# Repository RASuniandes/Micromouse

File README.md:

<h1 align="center">RAS Uniandes  - Micromouse 🐭🧀</h1>

### The autonomous maze-solving robot:

- SoB built around the STM32F405RGT6 
  - Wall detection based on peripheral infrared sensors and ToF
  - Position and speed control using magnetic encoders for Micro Metal Motors
  - IMU aided control
  - Bluetooth support
 
- Designed using KiCad
 
- Developed in the *Universidad de Los Andes* for the *Robotics and Automation Society* Chapter of the IEEE.

## Developed by: 
<ul>
  <li>Juan Sebastián Ortega Romero(https://github.com/tadzio8425)</li>
</ul>

## To do: 
- [x] Initial research regarding the state of the art of the competition
- [x] Selection of essential components 
- [x] Initial schematic design
- [x] Altium simulations
- [x] Infrared sensors breadboard testing
- [x] Schematic revisions and corrections
- [x] PCB Design and rule check
- [x] BOM File and quote requests
- [x] Final PCB revisions
- [x] Fabrication using the services of JLCPCB
- [x] Soldering components
- [x] Unitary tests
- [x] Coding Serial, USB and Bluetooth communications
- [x] Coding sensors
- [x] Coding a general version of the FloodFill algorithm in C
- [ ] Control and PID algorithm for position and speed
- [ ] Juncture of the control algorithm and FloodFill for maze solving
- [ ] Robot calibration in a real maze
- [ ] Development of external interfaces to ease communication with the robot

## Shematic

## PCB Design and 3D Render

| PCB | 3D |
| --- | --- |
|  |  | 

## Robot
| Initial Assembly | Final Version |
| --- | --- |
|  |  |

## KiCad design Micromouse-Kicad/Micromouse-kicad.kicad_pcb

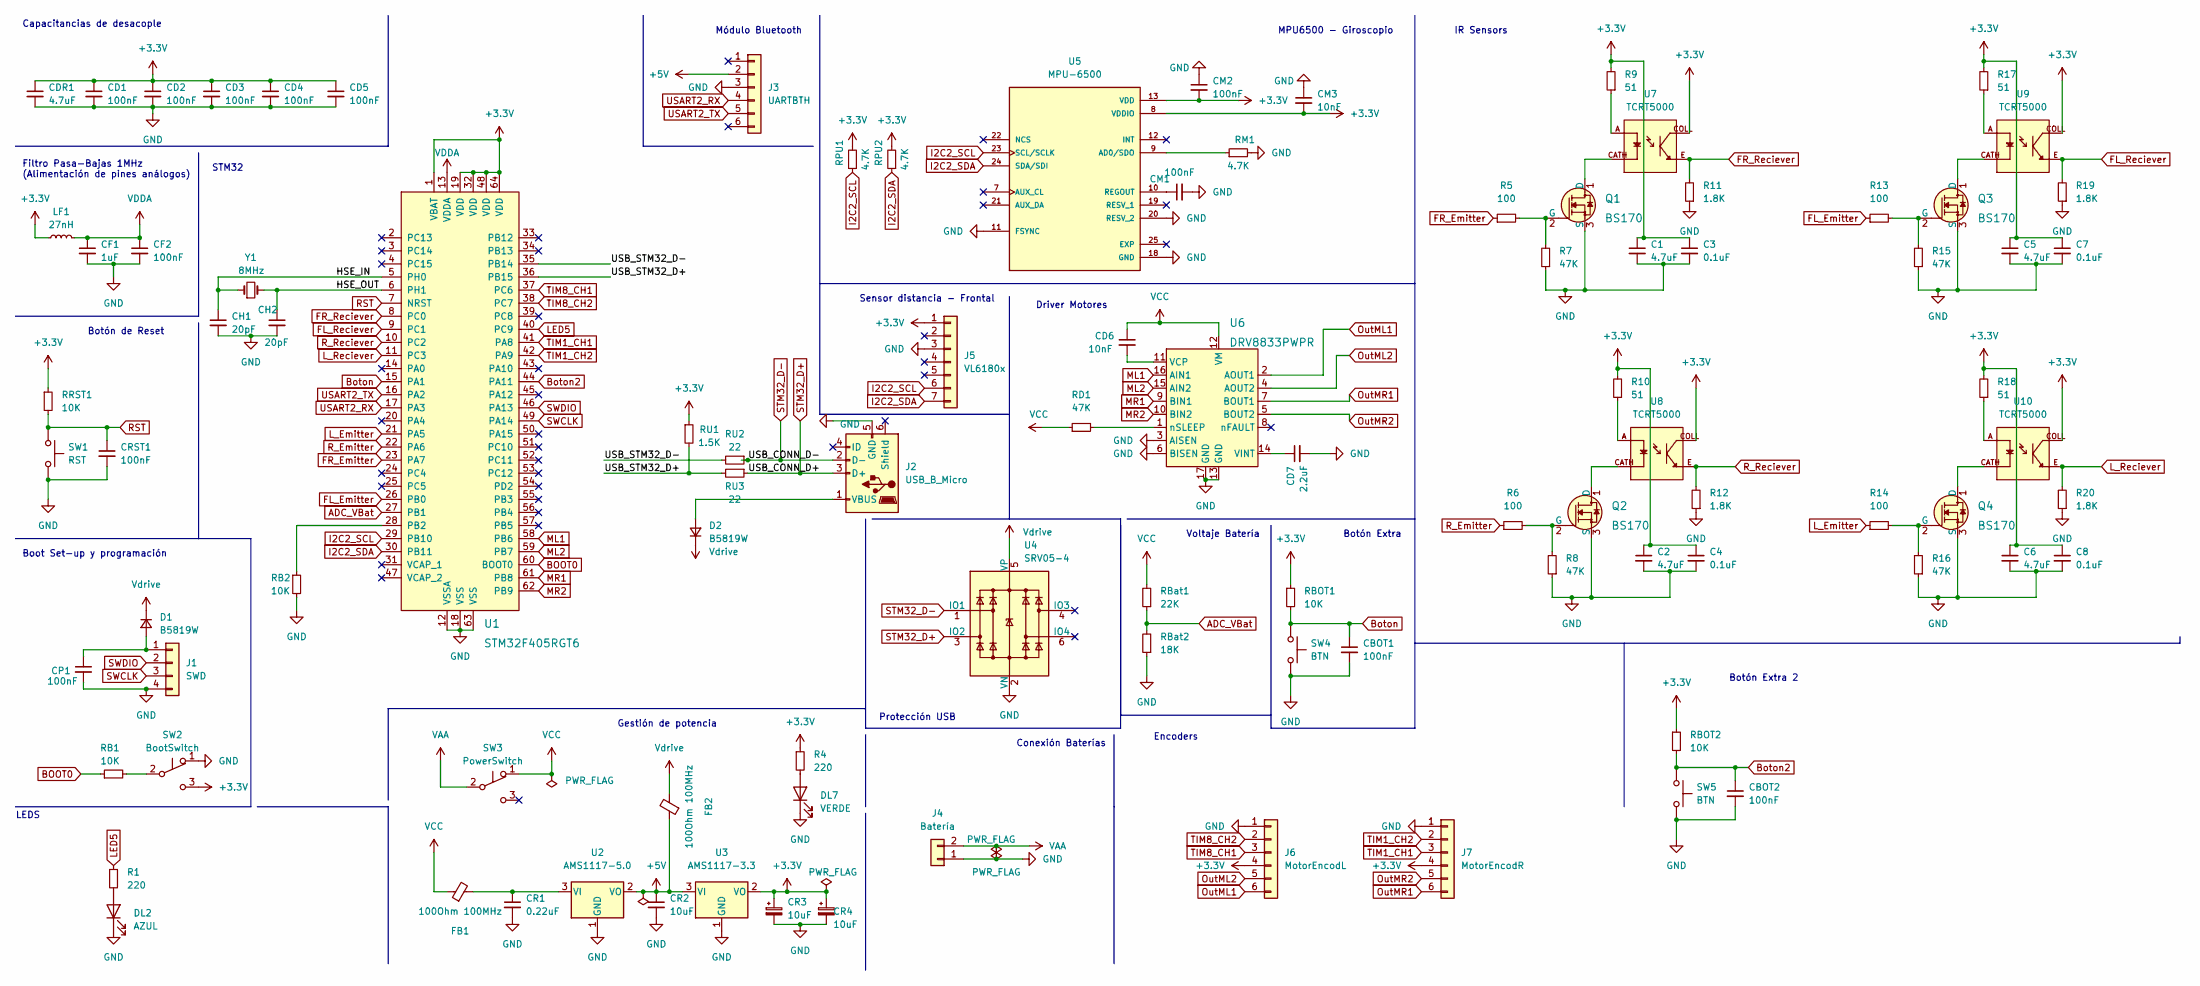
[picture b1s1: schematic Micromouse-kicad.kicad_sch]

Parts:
C1, C2, C5, C6: 4.7uF; C_0402_1005Metric
C3, C4, C7, C8: 0.1uF; C_0402_1005Metric
CBOT1, CBOT2: 100nF; C_0402_1005Metric
CD1, CD2, CD3, CD4, CD5: 100nF; C_0402_1005Metric
CD6: 10nF; C_0402_1005Metric
CD7: 2.2uF; C_0402_1005Metric
CDR1: 4.7uF; C_0402_1005Metric
CF1: 1uF; C_0402_1005Metric
CF2: 100nF; C_0402_1005Metric
CH1, CH2: 20pF; C_0402_1005Metric
CM1, CM2: 100nF; C_0402_1005Metric
CM3: 10nF; C_0402_1005Metric
CP1: 100nF; C_0402_1005Metric
CR1: 0.22uF; C_1206_3216Metric
CR2, CR3, CR4: 10uF; C_1206_3216Metric
CRST1: 100nF; C_0402_1005Metric
D1, D2: B5819W; D_SOD-123
DL2: AZUL; LED_0603_1608Metric
DL7: VERDE; LED_0603_1608Metric
FB1, FB2: 100Ohm 100MHz; L_0805_2012Metric
J1: SWD; PinHeader_1x04_P2.54mm_Vertical
J2: USB_B_Micro; MICRO-USB-SMD_5P-P0.65-H-F_MICRO5.9MMUSB
J3: UARTBTH; PinSocket_1x06_P2.54mm_Vertical
J4: Batería; AMASS_XT60-M
J5: VL6180x; PinSocket_1x07_P2.54mm_Vertical
J6: MotorEncodL; JST_SH_BM06B-SRSS-TB_1x06-1MP_P1.00mm_Vertical
J7: MotorEncodR; JST_SH_BM06B-SRSS-TB_1x06-1MP_P1.00mm_Vertical
LF1: 27nH; L_0402_1005Metric
Q1, Q2, Q3, Q4: BS170; TO-92-3; MPN BS170; Digi-Key_PN BS170-ND
R1, R4: 220; R_0603_1608Metric
R5, R6, R13, R14: 100; R_0402_1005Metric
R7, R8, R15, R16: 47K; R_0402_1005Metric
R9, R10, R17, R18: 51; R_0402_1005Metric
R11, R12, R19, R20: 1.8K; R_0402_1005Metric
RB1, RB2: 10K; R_0402_1005Metric
RBOT1, RBOT2: 10K; R_0402_1005Metric
RBat1: 22K; R_0402_1005Metric
RBat2: 18K; R_0402_1005Metric
RD1: 47K; R_0402_1005Metric
RM1: 4.7K; R_0402_1005Metric
RPU1, RPU2: 4.7K; R_0402_1005Metric
RRST1: 10K; R_0402_1005Metric
RU1: 1.5K; R_0402_1005Metric
RU2, RU3: 22; R_0603_1608Metric
SW1: RST; SW_PUSH_6mm_H5mm
SW2: BootSwitch; Switch_Slide
SW3: PowerSwitch; Switch_Slide
SW4, SW5: BTN; SW_PUSH_6mm_H5mm
U1: STM32F405RGT6; LQFP-64_10x10mm; MPN STM32F405RGT6; Digi-Key_PN 497-11767-ND
U2: AMS1117-5.0; SOT-223-3_TabPin2
U3: AMS1117-3.3; SOT-223-3_TabPin2
U4: SRV05-4; SOT-23-6
U5: MPU-6500; QFN40P300X300X95-25N; PARTREV 1.3
U6: DRV8833PWPR; TSSOP-16-1EP_W4.40mm; MPN DRV8833PWPR; Digi-Key_PN 296-29434-1-ND
U7, U8, U9, U10: TCRT5000; OPTO_TCRT5000; PARTREV 1.7
Y1: 8MHz; Crystal_SMD_5032-2Pin_5.0x3.2mm

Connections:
+3.3V: C1.1, C2.1, C3.1, C4.1, C5.1, C6.1, C7.1, C8.1, CD1.1, CD2.1, CD3.1, CD4.1, CD5.1, CDR1.1, CM2.2, CM3.2, CR3.1, CR4.1, J5.1, J6.4, J7.4, LF1.1, R4.1, R9.2, R10.2, R17.2, R18.2, RBOT1.1, RBOT2.1, RPU1.2, RPU2.2, RRST1.1, RU1.1, SW2.3 (C), U1.1 (VBAT), U1.19 (VDD), U1.32 (VDD), U1.48 (VDD), U1.64 (VDD), U3.2 (VO), U5.8 (VDDIO), U5.13 (VDD), U7.COLL, U8.COLL, U9.COLL, U10.COLL
+5V: CR2.1, FB2.1, J3.2, U2.2 (VO), U3.3 (VI)
/HSE_IN: CH1.1, U1.5 (PH0), Y1.1
/HSE_OUT: CH2.1, U1.6 (PH1), Y1.2
/USB_STM32_D+: RU1.2, RU3.2, U1.36 (PB15)
/USB_STM32_D-: RU2.2, U1.35 (PB14)
ADC_VBat: RBat1.1, RBat2.2, U1.27 (PB1)
BOOT0: RB1.1, U1.60 (BOOT0)
Boton: CBOT1.1, RBOT1.2, SW4.1, U1.15 (PA1)
Boton2: CBOT2.1, RBOT2.2, SW5.1, U1.44 (PA11)
FL_Emitter: R13.1, U1.26 (PB0)
FL_Reciever: R19.2, U1.9 (PC1), U9.E
FR_Emitter: R5.1, U1.23 (PA7)
FR_Reciever: R11.2, U1.8 (PC0), U7.E
GND: C1.2, C2.2, C3.2, C4.2, C5.2, C6.2, C7.2, C8.2, CBOT1.2, CBOT2.2, CD1.2, CD2.2, CD3.2, CD4.2, CD5.2, CD7.2, CDR1.2, CF1.2, CF2.2, CH1.2, CH2.2, CM1.2, CM2.1, CM3.1, CP1.2, CR1.2, CR2.2, CR3.2, CR4.2, CRST1.2, DL2.1 (K), DL7.1 (K), J1.4, J2.5 (GND), J3.3, J4.1, J5.3, J6.1, J7.1, Q1.3 (S), Q2.3 (S), Q3.3 (S), Q4.3 (S), R7.1, R8.1, R11.1, R12.1, R15.1, R16.1, R19.1, R20.1, RB2.2, RBat2.1, RM1.2, SW1.2, SW2.1 (A), SW4.2, SW5.2, U1.12 (VSSA), U1.18 (VSS), U1.63 (VSS), U2.1 (GND), U3.1 (GND), U4.2 (VN), U5.11 (FSYNC), U5.18 (GND), U5.20 (RESV_2), U6.3 (AISEN), U6.6 (BISEN), U6.13 (GND), U6.17 (GND)
I2C2_SCL: J5.6, RPU1.1, U1.29 (PB10), U5.23 (SCL/SCLK)
I2C2_SDA: J5.7, RPU2.1, U1.30 (PB11), U5.24 (SDA/SDI)
LED5: R1.1, U1.40 (PC9)
L_Emitter: R14.1, U1.21 (PA5)
L_Reciever: R20.2, U1.11 (PC3), U10.E
ML1: U1.58 (PB6), U6.16 (AIN1)
ML2: U1.59 (PB7), U6.15 (AIN2)
MR1: U1.61 (PB8), U6.9 (BIN1)
MR2: U1.62 (PB9), U6.10 (BIN2)
unnamed: CP1.1, D1.2 (A), J1.1
unnamed: D2.2 (A), J2.1 (VBUS)
unnamed: DL2.2 (A), R1.2
unnamed: DL7.2 (A), R4.2
unnamed: Q1.1 (D), U7.CATH
unnamed: Q1.2 (G), R5.2, R7.2
unnamed: Q2.1 (D), U8.CATH
unnamed: Q2.2 (G), R6.2, R8.2
unnamed: Q3.1 (D), U9.CATH
unnamed: Q3.2 (G), R13.2, R15.2
unnamed: Q4.1 (D), U10.CATH
unnamed: Q4.2 (G), R14.2, R16.2
unnamed: R9.1, U7.A
unnamed: R10.1, U8.A
unnamed: R17.1, U9.A
unnamed: R18.1, U10.A
unnamed: RB1.2, SW2.2 (B)
unnamed: RB2.1, U1.28 (PB2)
unnamed: CR1.1, FB1.2, U2.3 (VI)
unnamed: RM1.1, U5.9 (AD0/SDO)
unnamed: CM1.1, U5.10 (REGOUT)
unnamed: CD6.2, U6.11 (VCP)
unnamed: CD7.1, U6.14 (VINT)
unnamed: RD1.2, U6.1 (nSLEEP)
OutML1: J6.6, U6.2 (AOUT1)
OutML2: J6.5, U6.4 (AOUT2)
OutMR1: J7.6, U6.7 (BOUT1)
OutMR2: J7.5, U6.5 (BOUT2)
RST: CRST1.1, RRST1.2, SW1.1, U1.7 (NRST)
R_Emitter: R6.1, U1.22 (PA6)
R_Reciever: R12.2, U1.10 (PC2), U8.E
STM32_D+: J2.3 (D+), RU3.1, U4.3 (IO2)
STM32_D-: J2.2 (D-), RU2.1, U4.1 (IO1)
SWCLK: J1.3, U1.49 (PA14)
SWDIO: J1.2, U1.46 (PA13)
TIM1_CH1: J7.3, U1.41 (PA8)
TIM1_CH2: J7.2, U1.42 (PA9)
TIM8_CH1: J6.3, U1.37 (PC6)
TIM8_CH2: J6.2, U1.38 (PC7)
USART2_RX: J3.4, U1.17 (PA3)
USART2_TX: J3.5, U1.16 (PA2)
VAA: J4.2, SW3.2 (B)
VCC: CD6.1, FB1.1, RBat1.2, RD1.1, SW3.1 (A), U6.12 (VM)
VDDA: CF1.1, CF2.1, LF1.2, U1.13 (VDDA)
Vdrive: D1.1 (K), D2.1 (K), FB2.2, U4.5 (VP)

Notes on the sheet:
Protección USB
Voltaje Batería
LEDS
Gestión de potencia
Conexión Baterías
MPU6500 - Giroscopio
Botón Extra
STM32
IR Sensors
Módulo Bluetooth
Botón de Reset
Encoders
Botón Extra 2
Driver Motores
Capacitancias de desacople
Boot Set-up y programación
Filtro Pasa-Bajas 1MHz (Alimentación de pines análogos)
Sensor distancia - Frontal

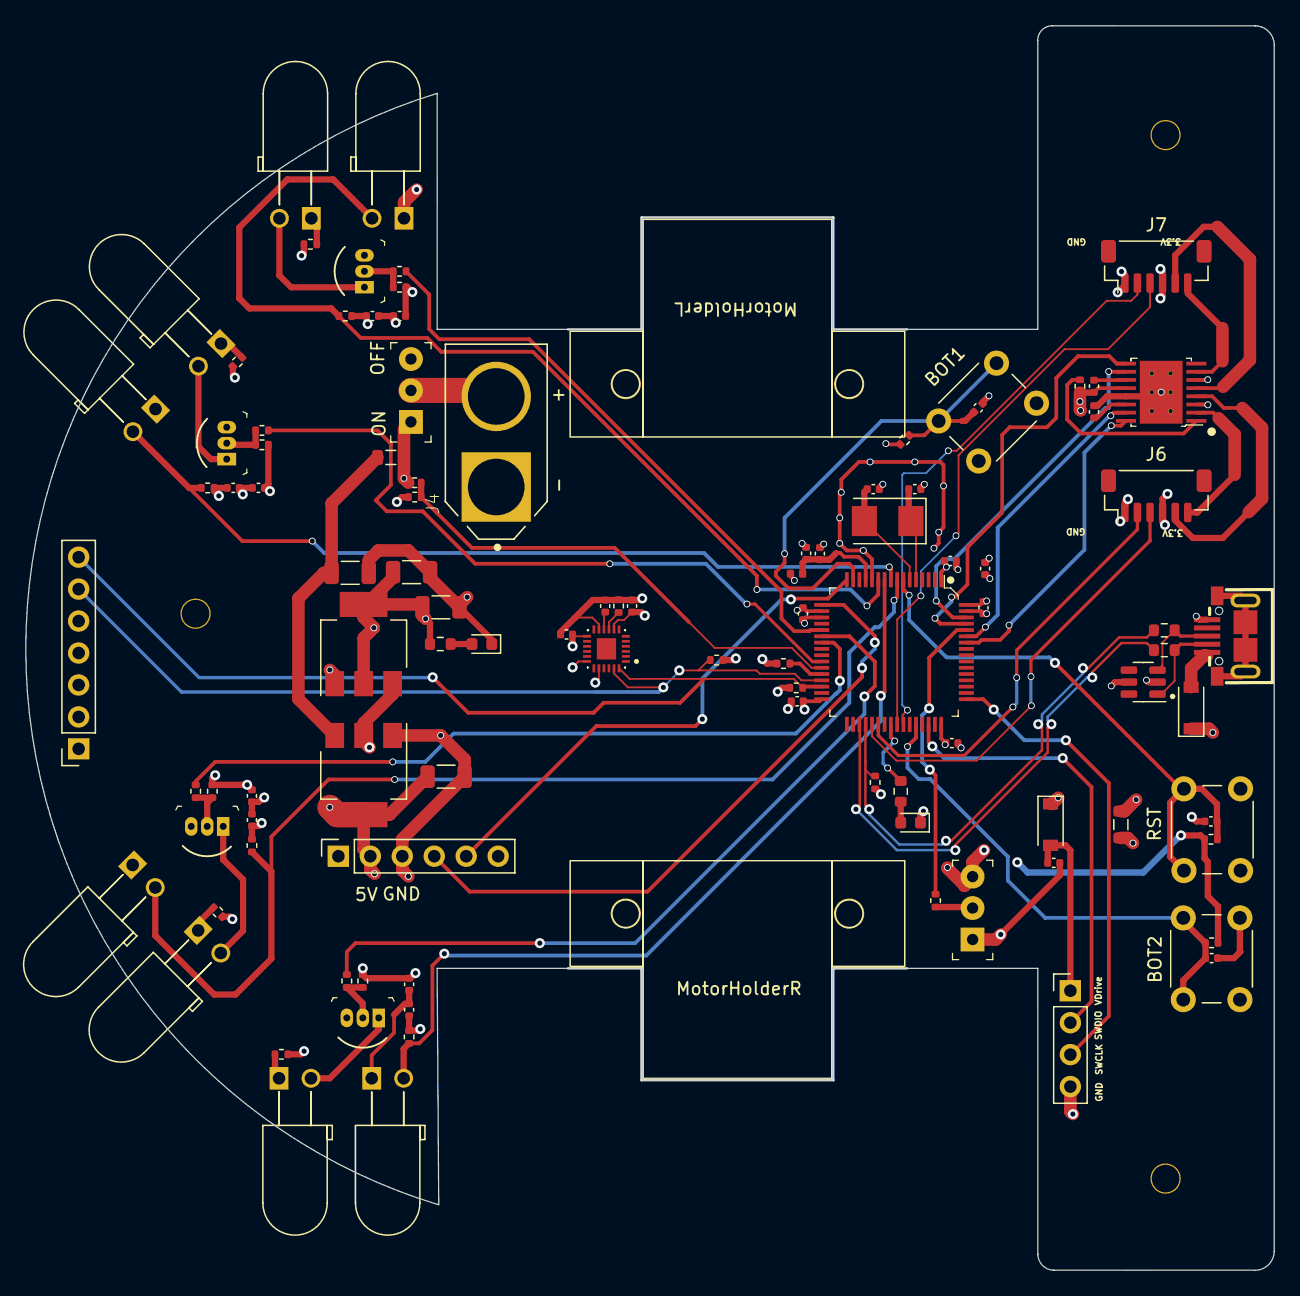
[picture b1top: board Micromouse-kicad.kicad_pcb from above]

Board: 4 copper layers, 99.1 x 98.8 mm, 99 parts (0 on the bottom side), 69 nets.

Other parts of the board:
MotorHolderL: Pololu; MotorHolder
MotorHolderR: Pololu; MotorHolder

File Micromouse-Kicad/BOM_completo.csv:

Id;Identificador;Empaquetado;Cantidad;Identificación;#Ref DigiKey ;Cantidad pedida;PPU ($);Total ($)
1;RBOT1,RB2,RBOT2,RRST1,RB1;R_0402_1005Metric;5;10K;RC1005F103CS;10;0.055;0.55
2;SW1;SW_PUSH_6mm_H5mm;1;RST;;;;0
3;R20,R11,R19,R12;R_0402_1005Metric;4;1.8K;RC0402FR-071K8L;10;0.014;0.14
4;CRST1,CP1,CF2,CM2,CD4,CBOT1,CBOT2,CD3,CM1,CD5,CD2,CD1;C_0402_1005Metric;12;100nF;;;;0
5;C6,CDR1,C1,C2,C5;C_0402_1005Metric;5;4.7uF;;;;0
6;U3;SOT-223-3_TabPin2;1;AMS1117-3.3;;;;0
7;Q1,Q4,Q3,Q2;TO-92-3;4;BS170;;;;0
8;RU1;R_0402_1005Metric;1;1.5K;RC0402FR-071K5L;10;0.014;0.14
9;RPU1,RM1,RPU2;R_0402_1005Metric;3;4.7K;AF0402FR-074K7L;10;0.053;0.53
10;R15,R16,R8,R7,RD1;R_0402_1005Metric;5;47K;AF0402FR-0747KL;10;0.053;0.53
11;DL7;LED_0603_1608Metric;1;VERDE;;;;0
12;U5;QFN40P300X300X95-25N;1;MPU-6500;1428-1011-1-ND;1;9.11;9.11
13;J2;MICRO-USB-SMD_5P-P0.65-H-F_MICRO5.9MMUSB;1;USB_B_Micro;;;;0
14;CD7;C_0402_1005Metric;1;2.2uF;;;;0
15;RU2,RU3;R_0603_1608Metric;2;22;;;;0
16;U6;TSSOP-16-1EP_W4.40mm;1;DRV8833PWPR;;;;0
17;LF1;L_0402_1005Metric;1;27nH;;;;0
18;CF1;C_0402_1005Metric;1;1uF;;;;0
19;R5,R13,R14,R6;R_0402_1005Metric;4;100;;;;0
20;R9,R18,R10,R17;R_0402_1005Metric;4;51;;;;0
21;U8,U9,U10,U7;OPTO_TCRT5000;4;TCRT5000;;;;0
22;C4,C8,C7,C3;C_0402_1005Metric;4;0.1uF;;;;0
23;J4;AMASS_XT60-M;1;BaterÃ­a;;;;0
24;CR4,CR3,CR2;C_1206_3216Metric;3;10uF;;;;0
25;SW2;Switch_Slide;1;BootSwitch;;;;0
26;FB1,FB2;L_0805_2012Metric;2;100Ohm 100MHz;;;;0
27;Y1;Crystal_SMD_5032-2Pin_5.0x3.2mm;1;8MHz;;;;0
28;MotorHolderR,MotorHolderL;MotorHolder;2;Pololu;;;;0
29;J3;PinSocket_1x06_P2.54mm_Vertical;1;UARTBTH;;;;0
30;DL2;LED_0603_1608Metric;1;AZUL;;;;0
31;J6;JST_SH_BM06B-SRSS-TB_1x06-1MP_P1.00mm_Vertical;1;MotorEncodL;;;;0
32;U2;SOT-223-3_TabPin2;1;AMS1117-5.0;;;;0
33;J5;PinSocket_1x07_P2.54mm_Vertical;1;VL6180x ;;;;0
34;SW5,SW4;SW_PUSH_6mm_H5mm;2;BTN;;;;0
35;U4;SOT-23-6;1;SRV05-4;;;;0
36;R1,R4;R_0603_1608Metric;2;220;;;;0
37;J7;JST_SH_BM06B-SRSS-TB_1x06-1MP_P1.00mm_Vertical;1;MotorEncodR;;;;0
38;CD6,CM3;C_0402_1005Metric;2;10nF;;;;0
39;D2,D1;D_SOD-123;2;B5819W;;;;0
40;RBat1;R_0402_1005Metric;1;22K;;;;0
41;RBat2;R_0402_1005Metric;1;18K;;;;0
42;SW3;Switch_Slide;1;PowerSwitch;;;;0
43;U1;LQFP-64_10x10mm;1;STM32F405RGT6;;;;0
44;CH1,CH2;C_0402_1005Metric;2;20pF;;;;0
45;CR1;C_1206_3216Metric;1;0.22uF;;;;0
46;J1;PinHeader_1x04_P2.54mm_Vertical;1;SWD;;;;0

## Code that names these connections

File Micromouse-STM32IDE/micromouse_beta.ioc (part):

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Mcu.Name=STM32F405RGTx
Mcu.Package=LQFP64
Mcu.UserName=STM32F405RGTx
PA1.GPIOParameters=GPIO_Label
PA1.GPIO_Label=BOTON1
PA1.Signal=GPIO_Input
PA11.GPIOParameters=GPIO_Label
PA11.GPIO_Label=BOTON2
PA11.Signal=GPIO_Input
PA13.Mode=Serial_Wire
PA13.Signal=SYS_JTMS-SWDIO
PA14.Mode=Serial_Wire
PA14.Signal=SYS_JTCK-SWCLK
PA2.Mode=Asynchronous
PA2.Signal=USART2_TX
PA3.Mode=Asynchronous
PA3.Signal=USART2_RX
PA5.GPIOParameters=GPIO_Label
PA5.GPIO_Label=R_Emitter
PA5.Signal=GPIO_Output
PA6.GPIOParameters=GPIO_Label
PA6.GPIO_Label=L_Emitter
PA6.Signal=GPIO_Output
PA7.GPIOParameters=GPIO_Label
PA7.GPIO_Label=FL_Emitter
PA7.Signal=GPIO_Output
PA8.Signal=S_TIM1_CH1
PA9.Signal=S_TIM1_CH2
PB0.GPIOParameters=GPIO_Label
PB0.GPIO_Label=FR_Emitter
PB0.Signal=GPIO_Output
PB1.GPIOParameters=GPIO_Label
PB1.GPIO_Label=vBat
PB1.Signal=ADCx_IN9
PB10.Mode=I2C
PB10.Signal=I2C2_SCL
PB11.Mode=I2C
PB11.Signal=I2C2_SDA
PB14.Mode=Device_Only_FS
PB14.Signal=USB_OTG_HS_DM
PB15.Mode=Device_Only_FS
PB15.Signal=USB_OTG_HS_DP
PB6.Signal=S_TIM4_CH1
PB7.Signal=S_TIM4_CH2
PB8.Signal=S_TIM4_CH3
PB9.Signal=S_TIM4_CH4
PC0.GPIOParameters=GPIO_Label
PC0.GPIO_Label=FL_Reciever
PC0.Signal=ADCx_IN10
PC1.GPIOParameters=GPIO_Label
PC1.GPIO_Label=FR_Reciever
PC1.Signal=ADCx_IN11
PC2.GPIOParameters=GPIO_Label
PC2.GPIO_Label=L_Reciever
PC2.Signal=ADCx_IN12
PC3.GPIOParameters=GPIO_Label
PC3.GPIO_Label=R_Reciever
PC3.Signal=ADCx_IN13
PC6.Signal=S_TIM8_CH1
PC7.Signal=S_TIM8_CH2
PC9.GPIOParameters=GPIO_Label
PC9.GPIO_Label=BLUE
PC9.Signal=GPIO_Output
PH0-OSC_IN.Mode=HSE-External-Oscillator
PH0-OSC_IN.Signal=RCC_OSC_IN
PH1-OSC_OUT.Mode=HSE-External-Oscillator
PH1-OSC_OUT.Signal=RCC_OSC_OUT
RCC.HSE_VALUE=8000000
RCC.SYSCLKFreq_VALUE=168000000
RCC.SYSCLKSource=RCC_SYSCLKSOURCE_PLLCLK
board=custom

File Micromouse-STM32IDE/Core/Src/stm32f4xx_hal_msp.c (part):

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
    __HAL_RCC_GPIOC_CLK_ENABLE();
    /**ADC1 GPIO Configuration
    PC0     ------> ADC1_IN10
    PC1     ------> ADC1_IN11
    PC2     ------> ADC1_IN12
    PC3     ------> ADC1_IN13
    */
    GPIO_InitStruct.Pin = FL_Reciever_Pin|FR_Reciever_Pin|L_Reciever_Pin|R_Reciever_Pin;
    GPIO_InitStruct.Mode = GPIO_MODE_ANALOG;
    GPIO_InitStruct.Pull = GPIO_NOPULL;
    HAL_GPIO_Init(GPIOC, &GPIO_InitStruct);
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
    __HAL_RCC_GPIOB_CLK_ENABLE();
    /**ADC2 GPIO Configuration
    PB1     ------> ADC2_IN9
    */
    GPIO_InitStruct.Pin = vBat_Pin;
    GPIO_InitStruct.Mode = GPIO_MODE_ANALOG;
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    __HAL_RCC_ADC1_CLK_DISABLE();

    /**ADC1 GPIO Configuration
    PC0     ------> ADC1_IN10
    PC1     ------> ADC1_IN11
    PC2     ------> ADC1_IN12
    PC3     ------> ADC1_IN13
    */
    HAL_GPIO_DeInit(GPIOC, FL_Reciever_Pin|FR_Reciever_Pin|L_Reciever_Pin|R_Reciever_Pin);

    /* ADC1 DMA DeInit */
    HAL_DMA_DeInit(hadc->DMA_Handle);
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    __HAL_RCC_ADC2_CLK_DISABLE();

    /**ADC2 GPIO Configuration
    PB1     ------> ADC2_IN9
    */
    HAL_GPIO_DeInit(vBat_GPIO_Port, vBat_Pin);

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
    __HAL_RCC_GPIOB_CLK_ENABLE();
    /**I2C2 GPIO Configuration
    PB10     ------> I2C2_SCL
    PB11     ------> I2C2_SDA
    */
    GPIO_InitStruct.Pin = GPIO_PIN_10|GPIO_PIN_11;
    GPIO_InitStruct.Mode = GPIO_MODE_AF_OD;
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    __HAL_RCC_I2C2_CLK_DISABLE();

    /**I2C2 GPIO Configuration
    PB10     ------> I2C2_SCL
    PB11     ------> I2C2_SDA
    */
    HAL_GPIO_DeInit(GPIOB, GPIO_PIN_10);

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
    __HAL_RCC_GPIOA_CLK_ENABLE();
    /**TIM1 GPIO Configuration
    PA8     ------> TIM1_CH1
    PA9     ------> TIM1_CH2
    */
    GPIO_InitStruct.Pin = GPIO_PIN_8|GPIO_PIN_9;
    GPIO_InitStruct.Mode = GPIO_MODE_AF_PP;
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
    __HAL_RCC_GPIOC_CLK_ENABLE();
    /**TIM8 GPIO Configuration
    PC6     ------> TIM8_CH1
    PC7     ------> TIM8_CH2
    */
    GPIO_InitStruct.Pin = GPIO_PIN_6|GPIO_PIN_7;
    GPIO_InitStruct.Mode = GPIO_MODE_AF_PP;
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
    __HAL_RCC_GPIOB_CLK_ENABLE();
    /**TIM4 GPIO Configuration
    PB6     ------> TIM4_CH1
    PB7     ------> TIM4_CH2
    PB8     ------> TIM4_CH3
    PB9     ------> TIM4_CH4
    */
    GPIO_InitStruct.Pin = GPIO_PIN_6|GPIO_PIN_7|GPIO_PIN_8|GPIO_PIN_9;
    GPIO_InitStruct.Mode = GPIO_MODE_AF_PP;
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    __HAL_RCC_TIM1_CLK_DISABLE();

    /**TIM1 GPIO Configuration
    PA8     ------> TIM1_CH1
    PA9     ------> TIM1_CH2
    */
    HAL_GPIO_DeInit(GPIOA, GPIO_PIN_8|GPIO_PIN_9);

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    __HAL_RCC_TIM8_CLK_DISABLE();

    /**TIM8 GPIO Configuration
    PC6     ------> TIM8_CH1
    PC7     ------> TIM8_CH2
    */
    HAL_GPIO_DeInit(GPIOC, GPIO_PIN_6|GPIO_PIN_7);

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
    __HAL_RCC_GPIOA_CLK_ENABLE();
    /**USART2 GPIO Configuration
    PA2     ------> USART2_TX
    PA3     ------> USART2_RX
    */
    GPIO_InitStruct.Pin = GPIO_PIN_2|GPIO_PIN_3;
    GPIO_InitStruct.Mode = GPIO_MODE_AF_PP;
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    __HAL_RCC_USART2_CLK_DISABLE();

    /**USART2 GPIO Configuration
    PA2     ------> USART2_TX
    PA3     ------> USART2_RX
    */
    HAL_GPIO_DeInit(GPIOA, GPIO_PIN_2|GPIO_PIN_3);

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
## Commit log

2022-12-23 readme creado
2022-12-23 readme creaso
2022-12-23 Commit inicial
2022-12-24 Avance esquemático - STM32, MPU6500, Driver Motores
2022-12-24 Esquemático con componentes básicos
2022-12-24 Huellas agregadas
2022-12-26 Avance PCB - Forma y motores
2022-12-27 Motores routeados
2022-12-27 MPU6500 routeado
2022-12-27 Casi todo routeado
2022-12-27 PCB Completa - Depurada
2022-12-27 Arreglo silkscreen
2022-12-27 Gerber generados
2022-12-27 BOM provisional
2022-12-27 Primera iteración finalizada
2022-12-27 Modelo 3D
2022-12-27 Sensor IR Modelado
2022-12-27 Cabra
2022-12-27 Ajuste VL180X
2023-01-06 Arreglao
2023-01-06 Vias y caminos borrados
2023-01-07 BOM Digikey
2023-01-07 Blackpill incluida
2023-01-07 Esquemático simplificado
2023-01-08 Micromouse con Blackpill routeado!
2023-01-08 Modelos 3D completados
2023-01-08 Arreglo bluetooth
2023-01-08 Pre-merge
2023-06-08 arreglo módulo frontal
2023-06-08 arreglo conector potencia
2023-06-08 Componentes listos
2023-06-08 Arreglos pines stm32
2023-06-09 Fabricado!
2023-06-11 modelos actualizados
2023-06-11 Modelo 3D listo
2023-06-13 Código primera versión
2023-06-18 Avance algoritmo: FloodFill
2023-06-18 It1 FloodFill: Llega con éxito a la meta
2023-06-18 Bug fix
2023-06-18 floodFill inicial terminado
2023-06-18 bug movimiento
2023-06-18 Bug arreglado - MM se mueve en 1 casilla
2023-06-19 Prueba con multiple runs
2023-06-19 Decisiones priorizadas
2023-08-03 modelos 3D en Kicad
2023-08-03 Pruebas de control inicial motores

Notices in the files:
Micromouse-STM32IDE/Core/Src/stm32f4xx_hal_msp.c:
Copyright (c) 2023 STMicroelectronics.
All rights reserved.
This software is licensed under terms that can be found in the LICENSE file
